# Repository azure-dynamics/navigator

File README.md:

# Navigator

**Flight-controller Pi HAT for Azure Dynamics' Radiance ROV**

Navigator is a Raspberry Pi HAT designed to host the low-level flight controller for the Radiance ROV. It manages communication between the Raspberry Pi and the ROV's hardware, monitoring system power and routing control signals.

---

## Features

* **Flight Control:** Powered by an ESP32-S3 processor.
* **Power Management:** On-board voltage regulation supplying power directly to the Raspberry Pi and HAT logic.
* **Propulsion Signals:** Six dedicated ESC signal outputs for motor control.
* **Sensor Integration:** Includes battery voltage monitoring and I2C expansion support for added sensors (such as an IMU).
* **Mission Computer Link:** Direct hardware UART communication with the Raspberry Pi.
* **Standard Footprint:** Designed to fit the standard Raspberry Pi HAT layout with mounting holes.

---

## Board Layout & Architecture

* **Layers:** 4-layer board design.
* **Component Placement:** Most components are located on the top side, with connectors and support resistors positioned underneath.
* **Connectivity:** Features a USB-C port for programming and debugging, alongside the main Raspberry Pi GPIO header connection.

---

## Project Status

* **Schematic:** In progress (Revision 003)
* **Layout:** Not complete
* **Fabrication:** Not yet ordered

---

## Repository Layout

```text
navigator/
├── hardware/       KiCad project and local symbol/footprint libraries
├── fabrication/    Manufacturing outputs (BOM, Gerbers, drill files)
├── firmware/       Flight-controller code
├── docs/           Project documentation
├── LICENSE
└── README.md
```

### Local Libraries

* `hardware/library/282837-2/` — TE 282837-2 connector footprint and STEP model.
* `hardware/library/BNO086/` — BNO086 IMU symbol and footprint.
* `hardware/library/logo/` — Board logo footprint.

---

## License

Copyright (C) 2026 Azure Dynamics.

This project is licensed under the
[CERN Open Hardware Licence Version 2 - Strongly Reciprocal](LICENSE)
(`CERN-OHL-S-2.0`). See [LICENSE](LICENSE) for the full text.

Third-party symbols, footprints, and STEP models in `hardware/library/` are
included for convenience and remain subject to their original terms.

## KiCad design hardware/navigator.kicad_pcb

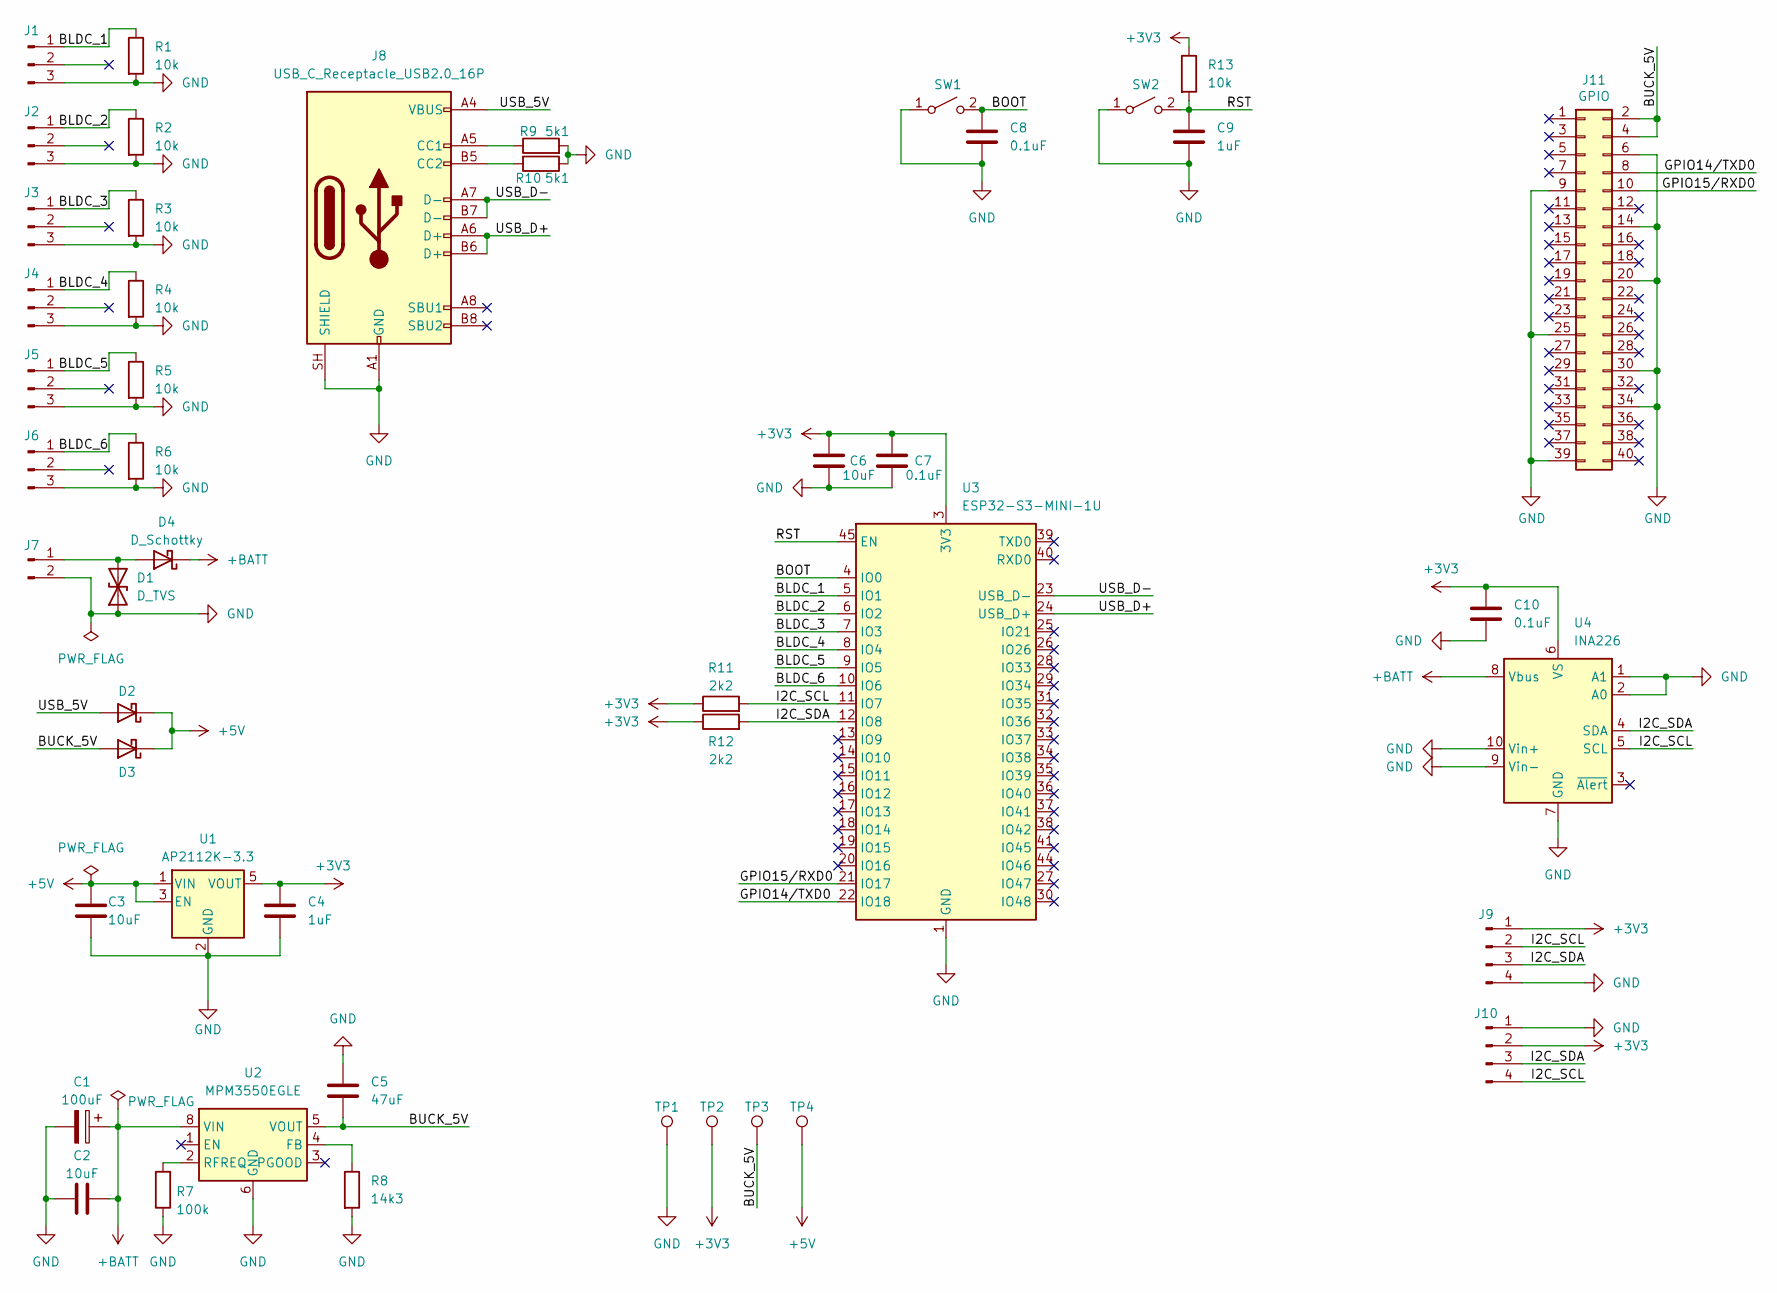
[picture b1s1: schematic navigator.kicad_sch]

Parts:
C1: 100uF; CP_Elec_8x10.5; DigiKey_PN PCE3809CT-ND
C2: 10uF; C_1210_3225Metric; DigiKey_PN 1276-3387-1-ND
C3, C6: 10uF; C_0805_2012Metric; DigiKey_PN 490-GRM21BC81C106MA73LCT-ND
C4, C9: 1uF; C_0805_2012Metric; DigiKey_PN 490-1695-1-ND
C5: 47uF; C_1210_3225Metric; DigiKey_PN 490-6538-1-ND
C7, C8, C10: 0.1uF; C_0805_2012Metric; DigiKey_PN 1276-1003-1-ND
D1: D_TVS; D_SMC; DigiKey_PN SMCJ26CALFCT-ND
D2, D3: D_Schottky; D_SOD-123; DigiKey_PN MBR0560TPMSCT-ND
D4: D_Schottky; Nexperia_CFP3_SOD-123W; DigiKey_PN 1801-SS36LWHCT-ND
J1, J2, J3, J4, J5, J6: BLDC-1; PinHeader_1x03_P2.54mm_Horizontal; DigiKey_PN 2057-PH1RB-03-UA-ND
J7: Conn_01x02_Pin; 282837-2; DigiKey_PN A113320-ND
J8: USB_C_Receptacle_USB2.0_16P; USB_C_Receptacle_Amphenol_12401948E412A; DigiKey_PN 664-12401948E412ACT-ND
J9: Conn_01x04_Pin; JST_GH_BM04B-GHS-TBT_1x04-1MP_P1.25mm_Vertical; DigiKey_PN 455-1566-1-ND
J10: Conn_01x04_Pin; JST_SH_BM04B-SRSS-TB_1x04-1MP_P1.00mm_Vertical; DigiKey_PN 455-BM04B-SRSS-TBCT-ND
J11: GPIO; PinSocket_2x20_P2.54mm_Vertical; DigiKey_PN 1528-2831-ND
R1, R2, R3, R4, R5, R6, R13: 10k; R_0805_2012Metric; DigiKey_PN RMCF0805JT10K0CT-ND
R7: 100k; R_0805_2012Metric; DigiKey_PN 311-100KARCT-ND
R8: 14k3; R_0805_2012Metric; DigiKey_PN 118-CR0805-FX-1432ELFCT-ND
R9, R10: 5k1; R_0805_2012Metric; DigiKey_PN RMCF0805JT5K10CT-ND
R11, R12: 2k2; R_0805_2012Metric; DigiKey_PN A106060CT-ND
SW1, SW2: SW_SPST; SW_SPST_TL3305A; DigiKey_PN EG5350CT-ND
TP1, TP2, TP3, TP4: TestPoint; TestPoint_Pad_1.5x1.5mm
U1: AP2112K-3.3; SOT-23-5; DigiKey_PN AP2112K-3.3TRG1DICT-ND
U2: MPM3550EGLE; MPS_LGA-18-10EP_12x12mm_P3.3mm; DigiKey_PN 1589-2043-ND
U3: ESP32-S3-MINI-1U; DigiKey_PN 1965-ESP32-S3-MINI-1U-N8CT-ND
U4: INA226; TSSOP-10_3x3mm_P0.5mm; DigiKey_PN 296-29034-1-ND

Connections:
+3V3: C4.1, C6.1, C7.1, C10.1, J9.1, J10.2, R11.1, R12.1, R13.1, TP2.1 (1_1), U1.5 (VOUT), U3.3 (3V3), U4.6 (VS)
+5V: C3.1, D2.1 (K), D3.1 (K), TP4.1 (1_1), U1.1 (VIN), U1.3 (EN)
+BATT: C1.1, C2.2, D4.1 (K), U2.8 (VIN), U4.8 (Vbus)
/BLDC_1: J1.1, R1.1, U3.5 (IO1)
/BLDC_2: J2.1, R2.1, U3.6 (IO2)
/BLDC_3: J3.1, R3.1, U3.7 (IO3)
/BLDC_4: J4.1, R4.1, U3.8 (IO4)
/BLDC_5: J5.1, R5.1, U3.9 (IO5)
/BLDC_6: J6.1, R6.1, U3.10 (IO6)
/BOOT: C8.1, SW1.2 (B), U3.4 (IO0)
/BUCK_5V: C5.2, D3.2 (A), J11.2, J11.4, TP3.1 (1_1), U2.5 (VOUT)
/GPIO14/TXD0: J11.8, U3.22 (IO18)
/GPIO15/RXD0: J11.10, U3.21 (IO17)
/I2C_SCL: J9.2, J10.4, R11.2, U3.11 (IO7), U4.5 (SCL)
/I2C_SDA: J9.3, J10.3, R12.2, U3.12 (IO8), U4.4 (SDA)
/RST: C9.1, R13.2, SW2.2 (B), U3.45 (EN)
/USB_5V: D2.2 (A), J8.A4 (VBUS), J8.A9 (VBUS), J8.B4 (VBUS), J8.B9 (VBUS)
/USB_D+: J8.A6 (D+), J8.B6 (D+), U3.24 (USB_D+)
/USB_D-: J8.A7 (D-), J8.B7 (D-), U3.23 (USB_D-)
GND: C1.2, C2.1, C3.2, C4.2, C5.1, C6.2, C7.2, C8.2, C9.2, C10.2, D1.1 (A1), J1.3, J2.3, J3.3, J4.3, J5.3, J6.3, J7.2, J8.A1 (GND), J8.A12 (GND), J8.B1 (GND), J8.B12 (GND), J8.SH (SHIELD), J9.4, J10.1, J11.6, J11.9, J11.14, J11.20, J11.25, J11.30, J11.34, J11.39, R1.2, R2.2, R3.2, R4.2, R5.2, R6.2, R7.1, R8.2, R9.2, R10.1, SW1.1 (A), SW2.1 (A), TP1.1 (1_1), U1.2 (GND), U2.6 (GND), U2.7 (GND), U2.9 (GND), U2.10 (GND), U2.11 (GND), U2.12 (GND), U2.13 (GND), U2.14 (GND), U2.15 (GND), U2.16 (GND), U2.17 (GND), U2.18 (GND), U3.1 (GND), U3.2 (GND), U3.42 (GND), U3.43 (GND), U3.46 (GND), U3.47 (GND), U3.48 (GND), U3.49 (GND), U3.50 (GND), U3.51 (GND), U3.52 (GND), U3.53 (GND), U3.54 (GND), U3.55 (GND), U3.56 (GND), U3.57 (GND), U3.58 (GND), U3.59 (GND), U3.60 (GND), U3.61 (GND), U3.62 (GND), U3.63 (GND), U3.64 (GND), U3.65 (GND), U4.1 (A1), U4.2 (A0), U4.7 (GND), U4.9 (Vin-), U4.10 (Vin+)
unnamed: D1.2 (A2), D4.2 (A), J7.1
unnamed: J8.A5 (CC1), R9.1
unnamed: J8.B5 (CC2), R10.2
unnamed: R8.1, U2.4 (FB)
unnamed: R7.2, U2.2 (RFREQ)

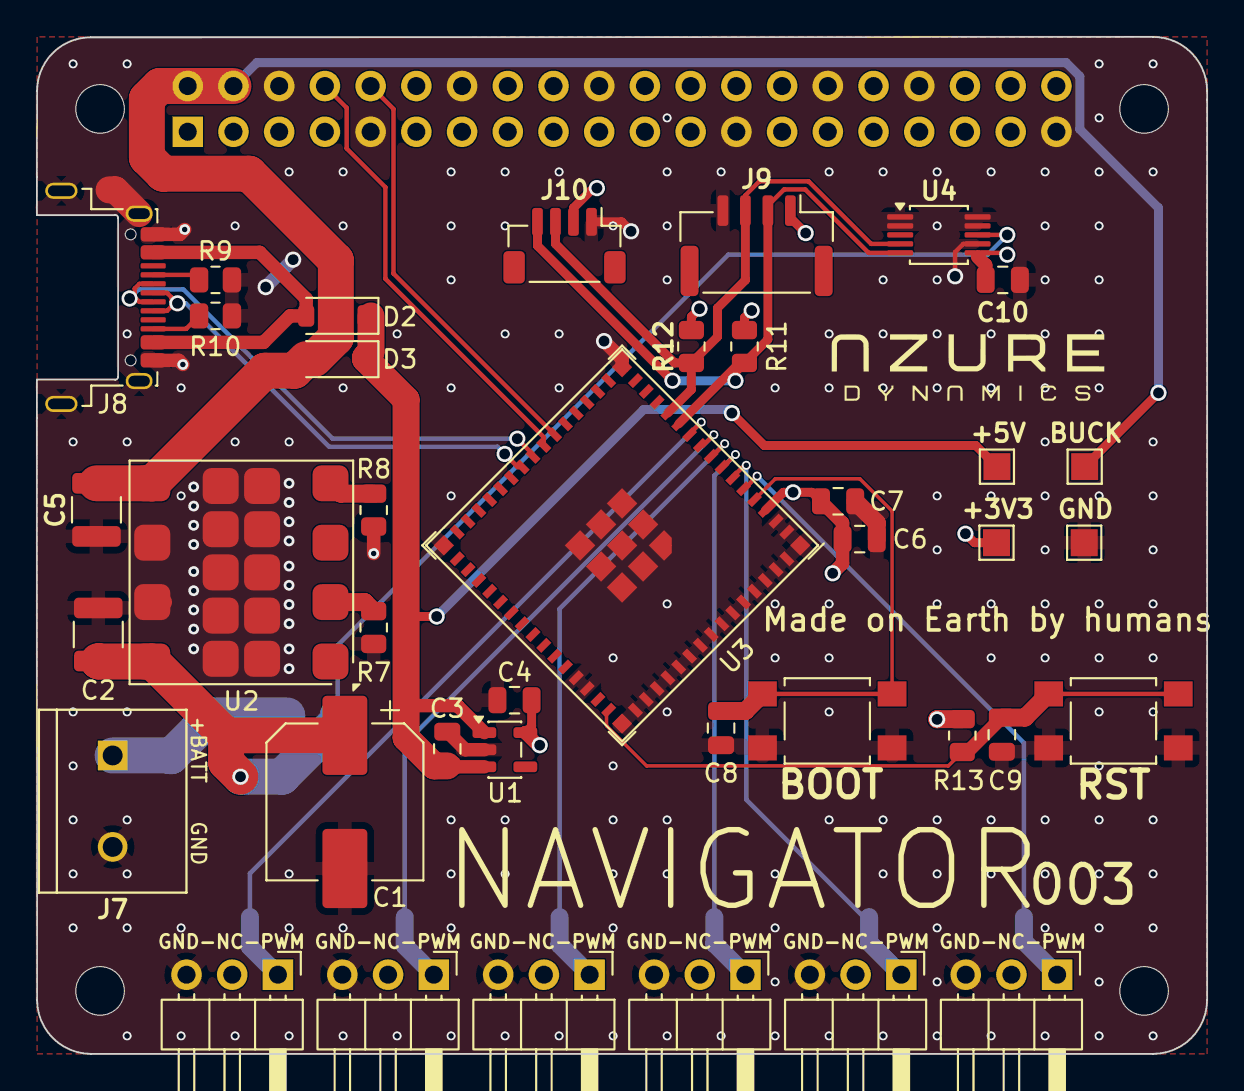
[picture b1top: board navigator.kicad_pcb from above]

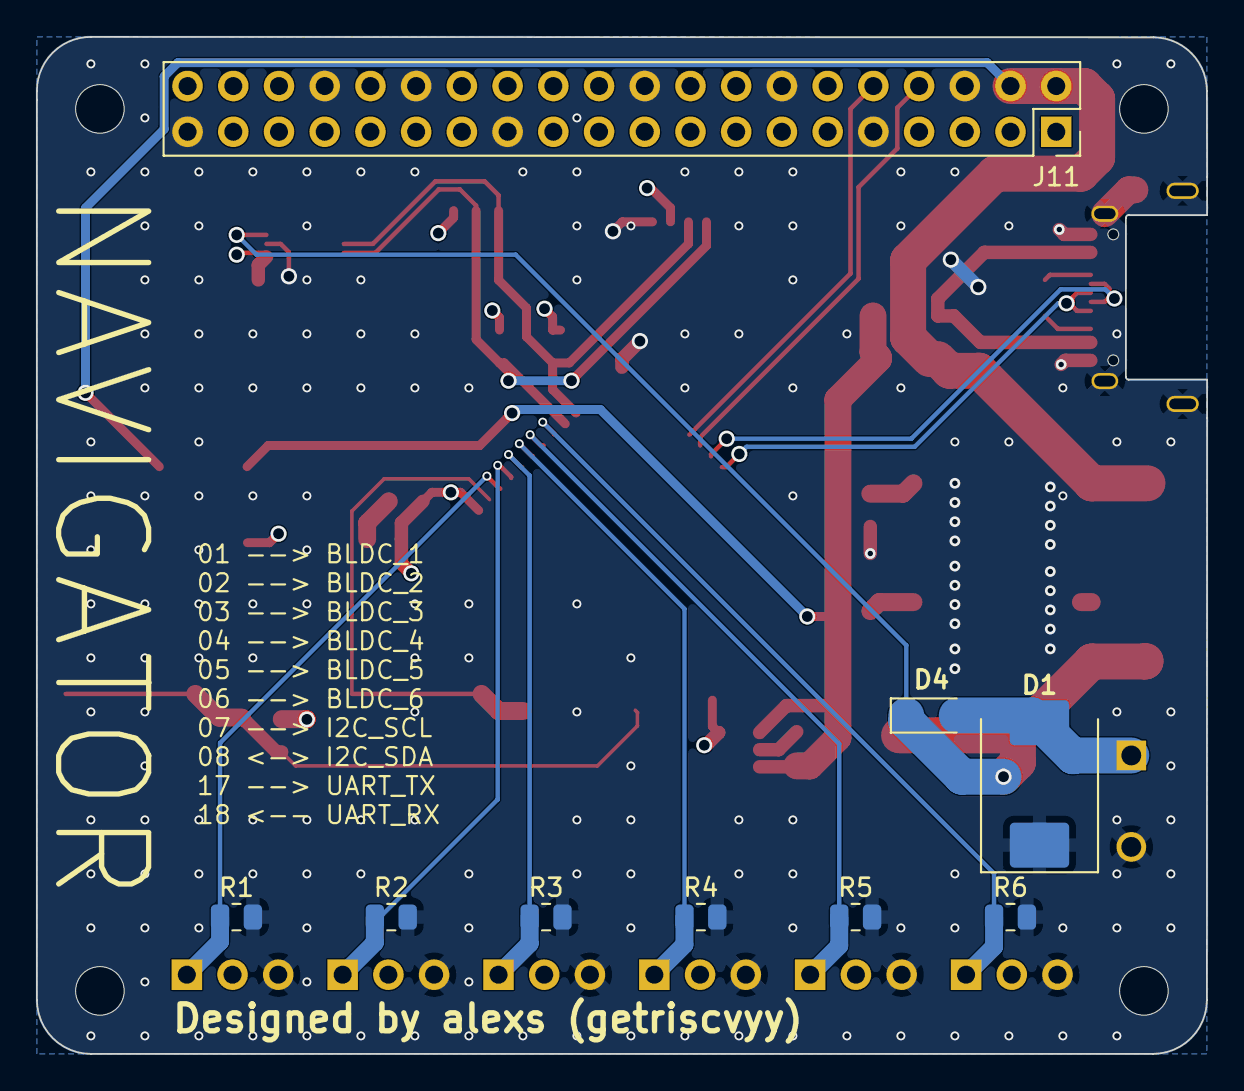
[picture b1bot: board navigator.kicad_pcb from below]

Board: 4 copper layers, 65.0 x 56.5 mm, 52 parts (9 on the bottom side), 25 nets.

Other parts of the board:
MH1, MH2, MH3, MH4: MountingHole_2.7mm_M2.5
